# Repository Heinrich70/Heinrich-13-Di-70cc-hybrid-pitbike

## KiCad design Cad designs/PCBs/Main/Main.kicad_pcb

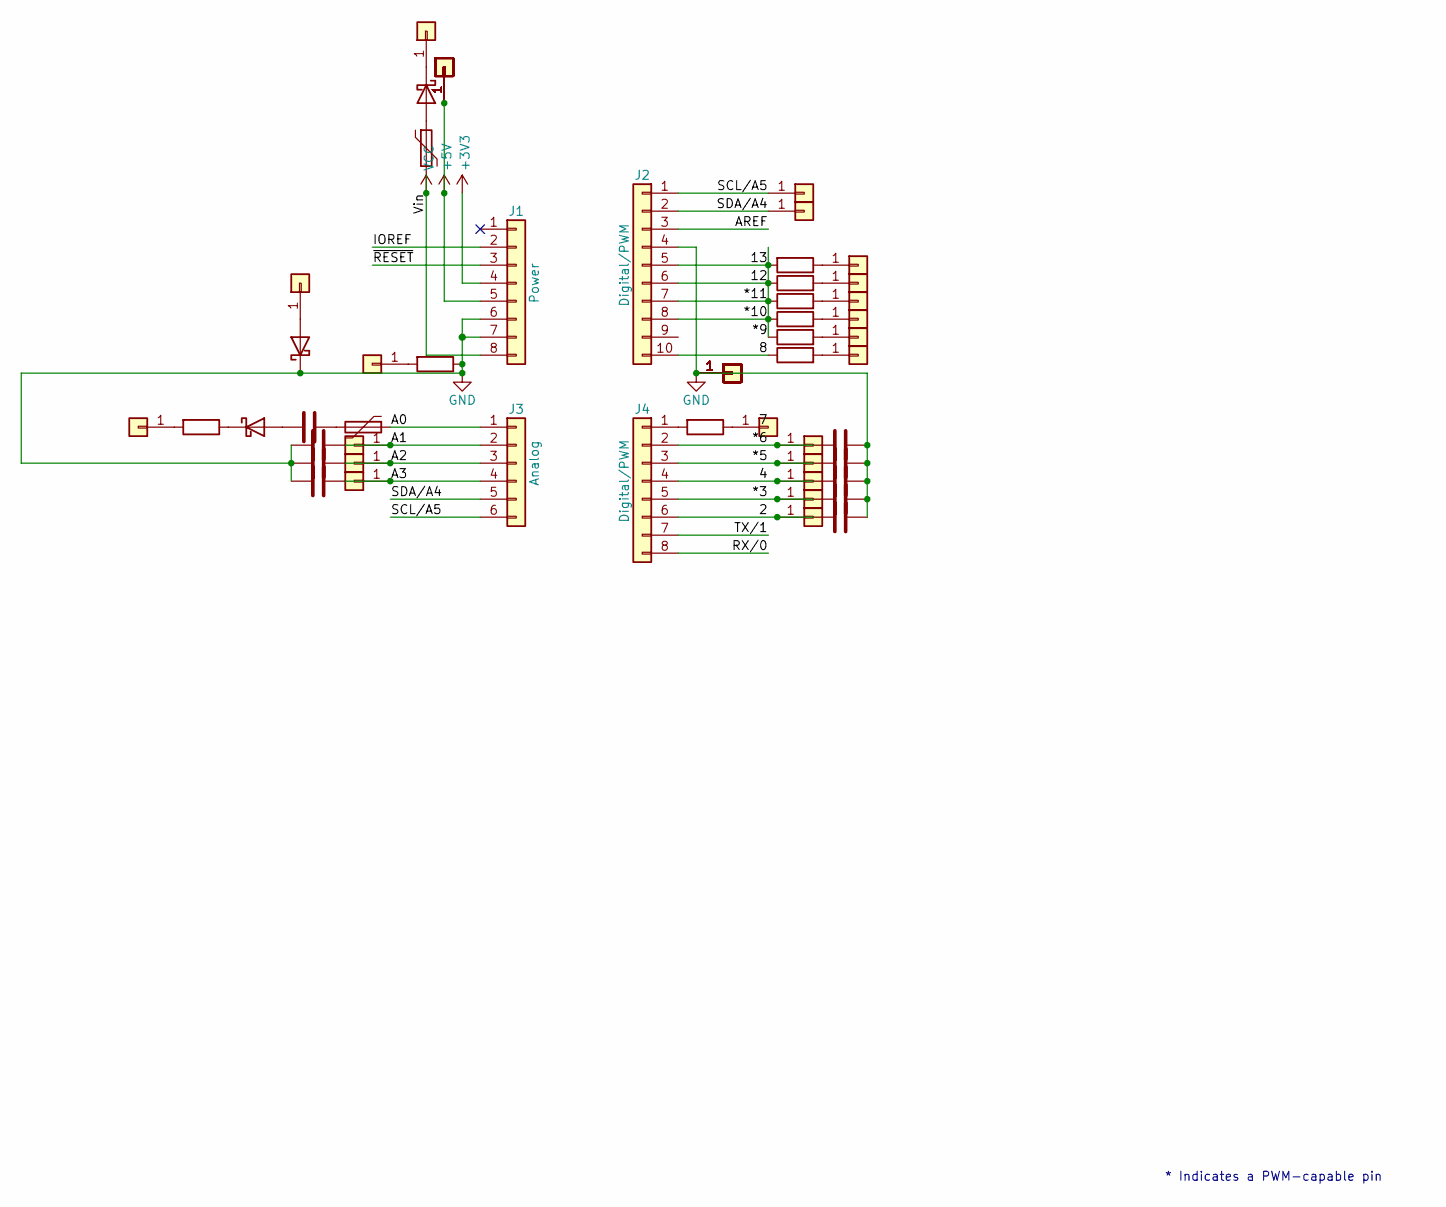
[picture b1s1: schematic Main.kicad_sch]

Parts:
C1, C2, C3, C4, C5, C6, C7, C8, C9: C; C_Disc_D5.0mm_W2.5mm_P2.50mm
D1, D2, D3: 1N5819; D_DO-201AD_P15.24mm_Horizontal
F1, F2: Polyfuse; Fuse_Bourns_MF-RHT050
J1: Power; PinSocket_1x08_P2.54mm_Vertical
J2: Digital/PWM; PinSocket_1x10_P2.54mm_Vertical
J3: Analog; PinSocket_1x06_P2.54mm_Vertical
J4: Digital/PWM; PinSocket_1x08_P2.54mm_Vertical
J5, J6, J7, J8, J9, J10, J11, J12, J13, J14, J15, J16, J17, J18, J19, J20, J21, J22, J23, J24, J25, J26, J27, J28, J29, J30, J31, J32, J33, J34, J35, J36, J37, J38, J39, J40, J41, J42, J43, J44, J45, J46, J47, J48, J49, J50: Conn_01x01; SolderWire-0.127sqmm_1x01_D0.48mm_OD1mm
R1, R2, R3, R4, R5, R6, R7, R8, R9: R; R_Axial_DIN0207_L6.3mm_D2.5mm_P7.62mm_Horizontal

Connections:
+3V3: J1.4
+5V: J1.5, J22.1 (Pin_1_1), J23.1 (Pin_1_1), J27.1 (Pin_1_1), J28.1 (Pin_1_1), J29.1 (Pin_1_1), J33.1 (Pin_1_1), J34.1 (Pin_1_1), J35.1 (Pin_1_1), J36.1 (Pin_1_1)
/2: C5.1, J4.6, J43.1 (Pin_1_1)
/4: C7.1, J4.4, J41.1 (Pin_1_1)
/8: J2.10, R2.1
/*3: C8.1, J4.5, J42.1 (Pin_1_1)
/*5: C3.1, J4.3, J40.1 (Pin_1_1)
/*6: C4.1, J4.2, J39.1 (Pin_1_1)
/*10: J2.5, J2.6, J2.7, J2.8, R3.1, R4.1, R5.1, R6.1, R7.2
/A0: F2.1, J3.1
/A1: C9.1, J3.2, J44.1 (Pin_1_1)
/A2: C6.1, J3.3, J45.1 (Pin_1_1)
/A3: C2.1, J3.4, J46.1 (Pin_1_1)
/AREF: J2.3
/IOREF: J1.2
/RX/0: J4.8
/SCL/A5: J2.1, J3.6, J10.1 (Pin_1_1)
/SDA/A4: J2.2, J3.5, J31.1 (Pin_1_1)
/TX/1: J4.7
/~RESET: J1.3
GND: C2.2, C3.2, C4.2, C5.2, C6.2, C7.2, C8.2, C9.2, D3.1 (K), J1.6, J1.7, J2.4, J5.1 (Pin_1_1), J6.1 (Pin_1_1), J7.1 (Pin_1_1), J8.1 (Pin_1_1), J9.1 (Pin_1_1), J11.1 (Pin_1_1), J12.1 (Pin_1_1), J13.1 (Pin_1_1), J14.1 (Pin_1_1), J15.1 (Pin_1_1), J16.1 (Pin_1_1), J17.1 (Pin_1_1), J18.1 (Pin_1_1), J19.1 (Pin_1_1), J20.1 (Pin_1_1), J21.1 (Pin_1_1), R9.1
unnamed: C1.1, F2.2
unnamed: C1.2, D1.2 (A)
unnamed: D1.1 (K), R8.1
unnamed: D2.2 (A), F1.1
unnamed: D2.1 (K), J47.1 (Pin_1_1)
unnamed: D3.2 (A), J50.1 (Pin_1_1)
unnamed: J4.1, R1.2
unnamed: J24.1 (Pin_1_1), R2.2
unnamed: J25.1 (Pin_1_1), R3.2
unnamed: J26.1 (Pin_1_1), R6.2
unnamed: J30.1 (Pin_1_1), R4.2
unnamed: J32.1 (Pin_1_1), R1.1
unnamed: J37.1 (Pin_1_1), R7.1
unnamed: J38.1 (Pin_1_1), R5.2
unnamed: J48.1 (Pin_1_1), R8.2
unnamed: J49.1 (Pin_1_1), R9.2
VCC: F1.2, J1.8

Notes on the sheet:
* Indicates a PWM-capable pin

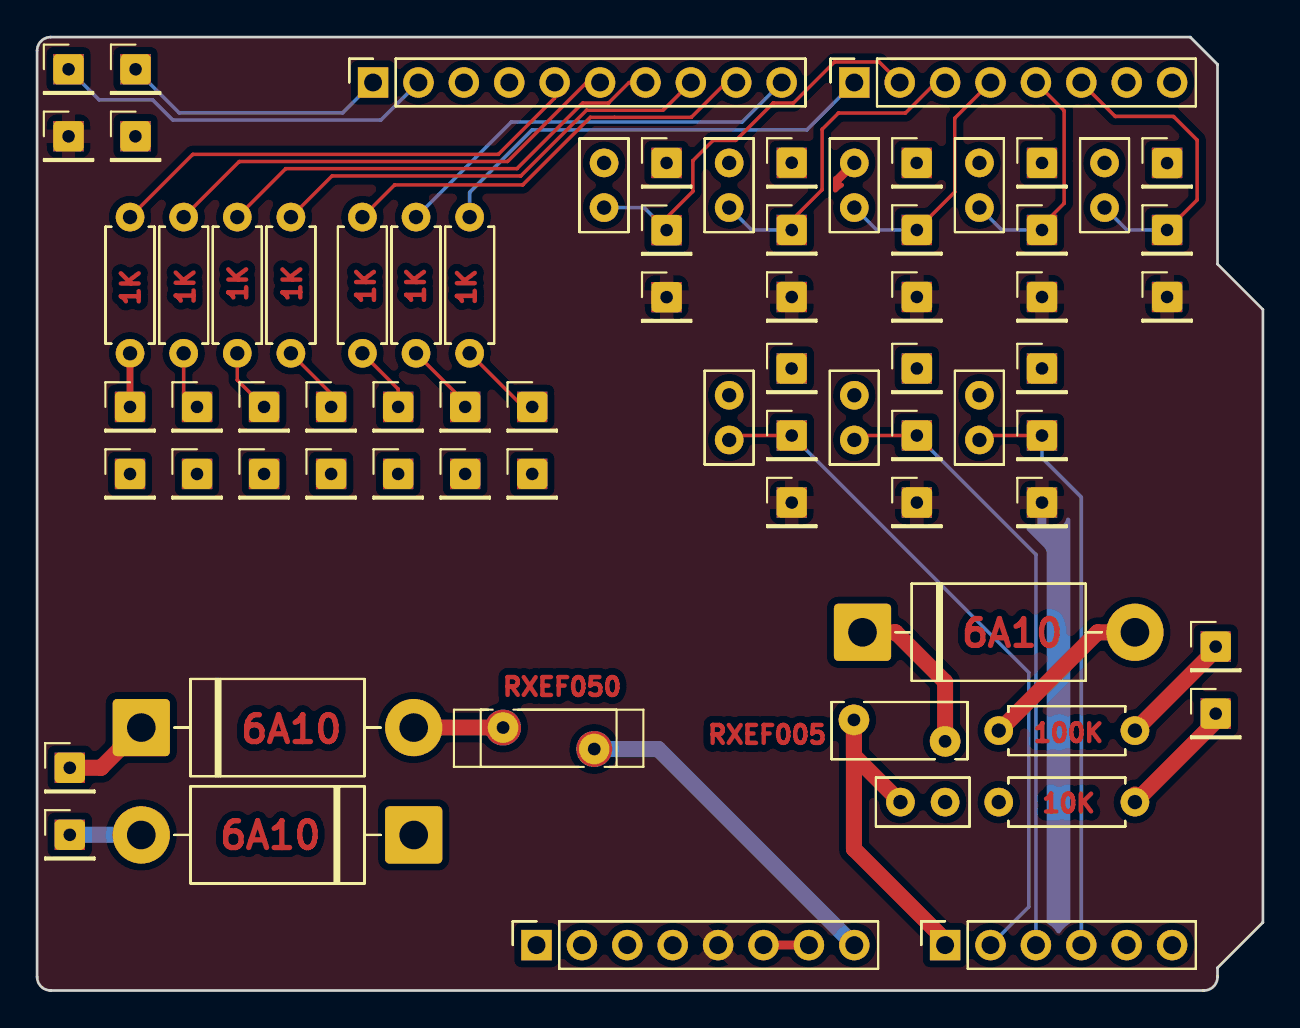
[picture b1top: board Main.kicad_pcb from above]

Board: 2 copper layers, 68.6 x 53.3 mm, 73 parts (0 on the bottom side), 32 nets.

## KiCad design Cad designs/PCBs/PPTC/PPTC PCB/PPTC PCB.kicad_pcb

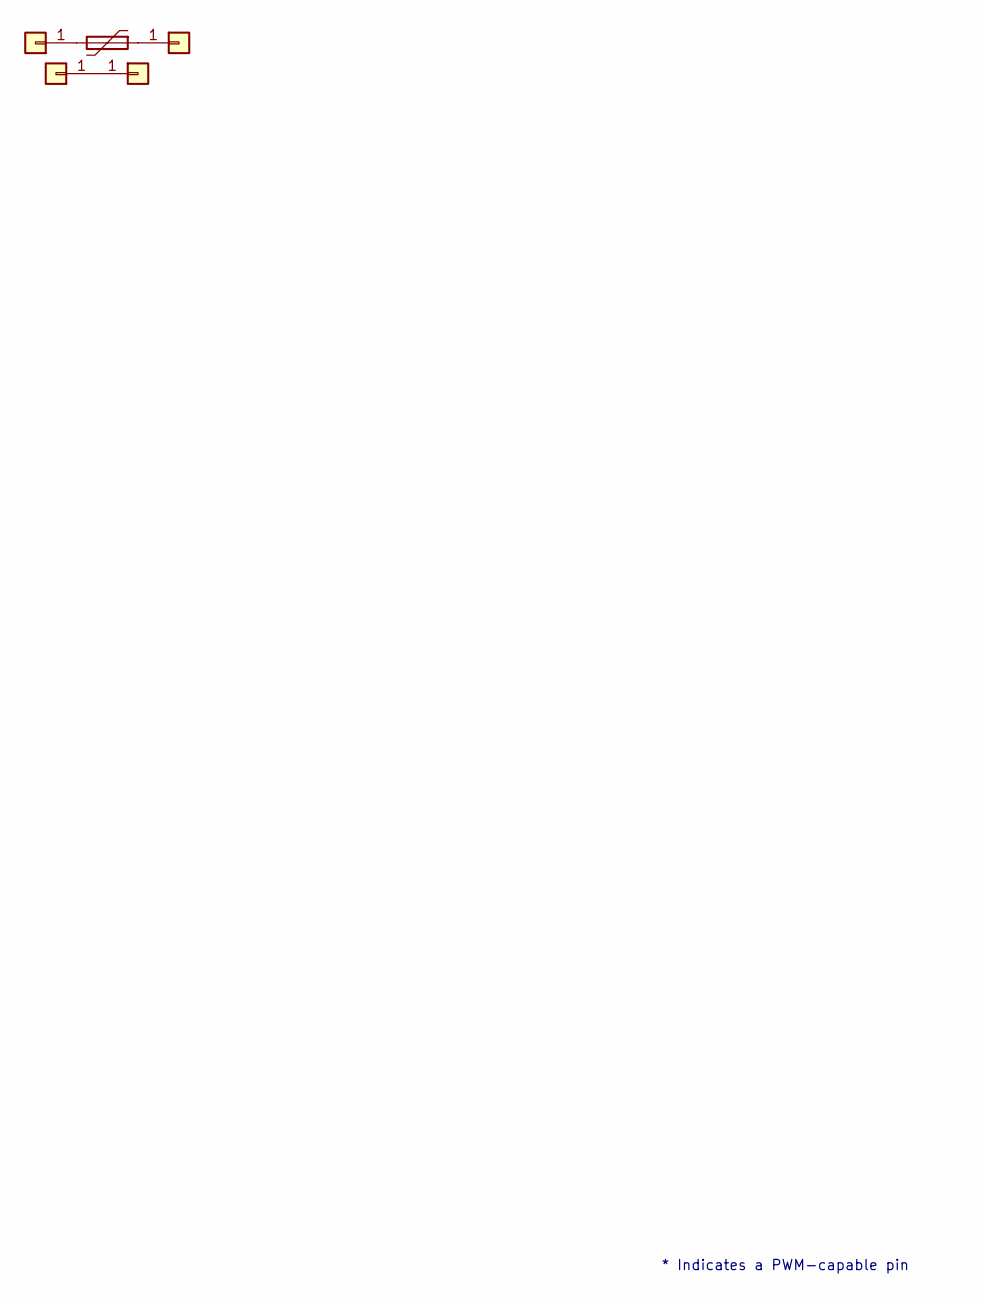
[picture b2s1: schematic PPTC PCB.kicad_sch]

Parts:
F1: Polyfuse; Fuse_Bourns_MF-RHT050
J1, J2, J3, J4: Conn_01x01; PinHeader_1x01_P1.00mm_Vertical

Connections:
unnamed: F1.2, J1.1 (Pin_1_1)
unnamed: J2.1 (Pin_1_1), J4.1 (Pin_1_1)
unnamed: F1.1, J3.1 (Pin_1_1)

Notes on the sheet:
* Indicates a PWM-capable pin

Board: 2 copper layers, 5 parts (0 on the bottom side), 3 nets, no tracks yet.

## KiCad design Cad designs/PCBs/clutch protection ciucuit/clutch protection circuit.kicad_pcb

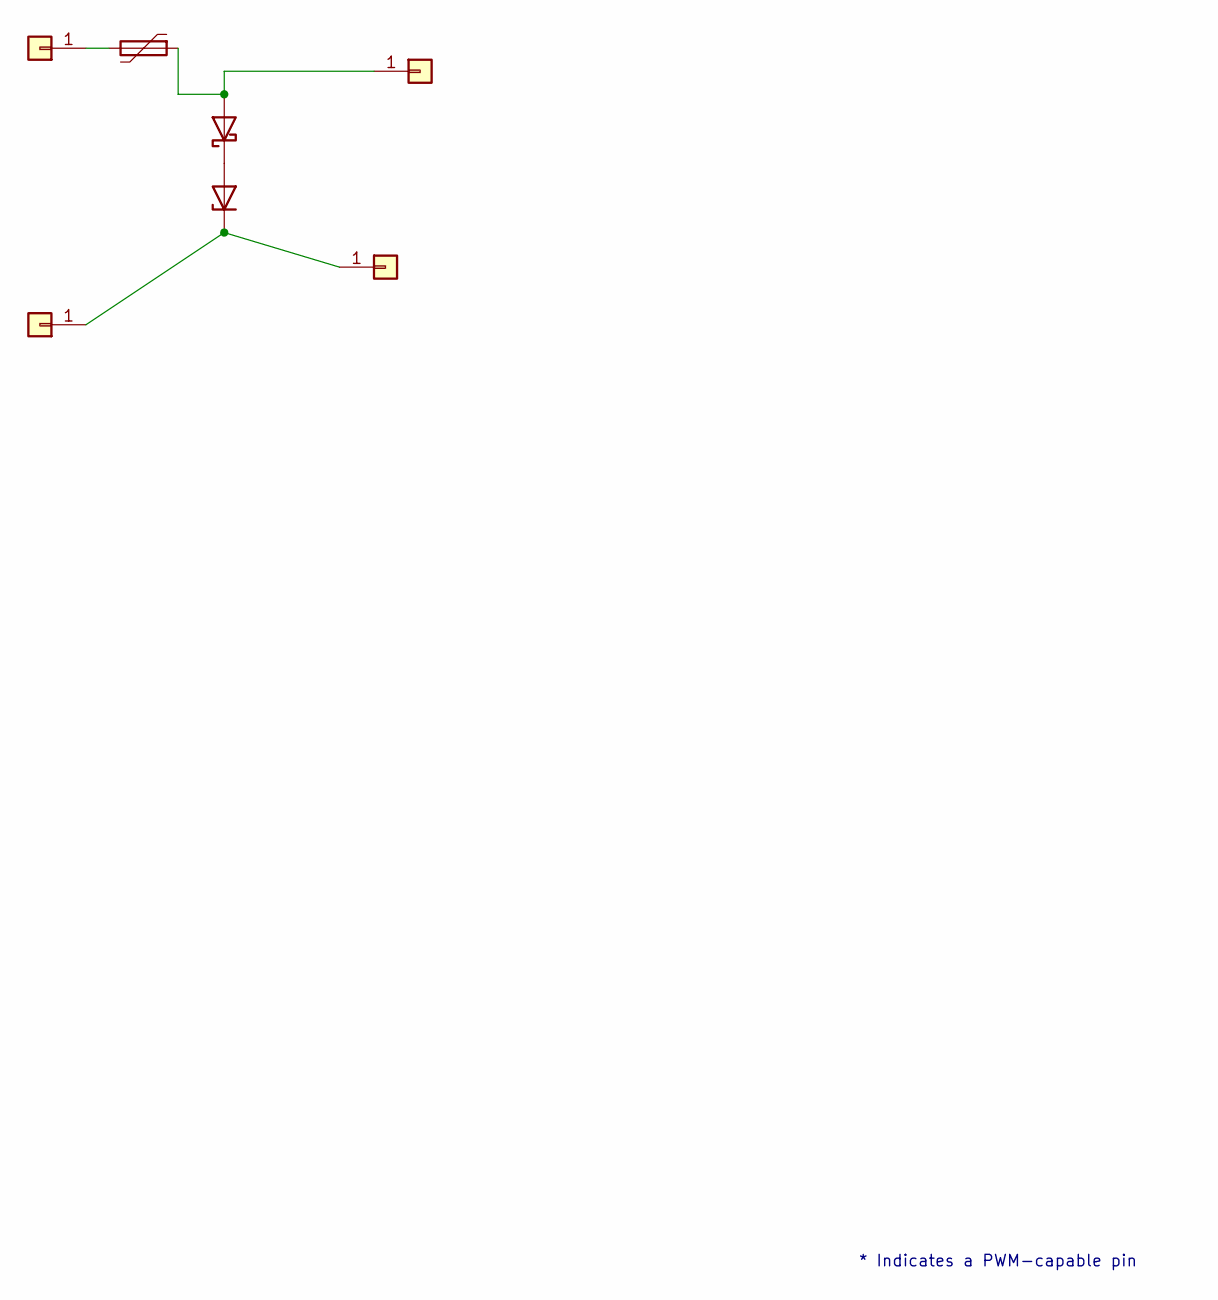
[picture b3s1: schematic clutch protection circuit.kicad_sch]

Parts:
D1: 1N47xxA; D_DO-41_SOD81_P10.16mm_Horizontal
D2: 1N5819; D_DO-41_SOD81_P10.16mm_Horizontal
F1: Polyfuse; Fuse_Bourns_MF-RHT050
J1, J2, J3, J4: Conn_01x01; PinHeader_1x01_P1.00mm_Vertical

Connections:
unnamed: D1.2 (A), D2.1 (K)
unnamed: D1.1 (K), J2.1 (Pin_1_1), J3.1 (Pin_1_1)
unnamed: D2.2 (A), F1.1, J1.1 (Pin_1_1)
unnamed: F1.2, J4.1 (Pin_1_1)

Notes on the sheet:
* Indicates a PWM-capable pin

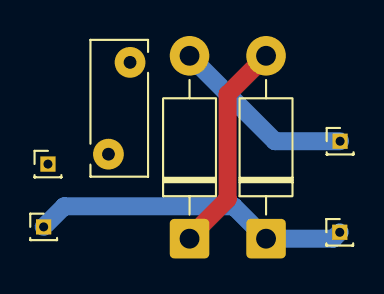
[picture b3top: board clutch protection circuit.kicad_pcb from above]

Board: 2 copper layers, 7 parts (0 on the bottom side), 4 nets.

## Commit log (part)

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2026-05-24 24/05/26
2026-05-24 clutch cover assesmbly
2026-05-24 goodnight
2026-05-25 25/05/26
2026-05-26 26/05/26
2026-06-01 02/06/26
2026-06-07 07/06/26
2026-06-16 17/06/26
